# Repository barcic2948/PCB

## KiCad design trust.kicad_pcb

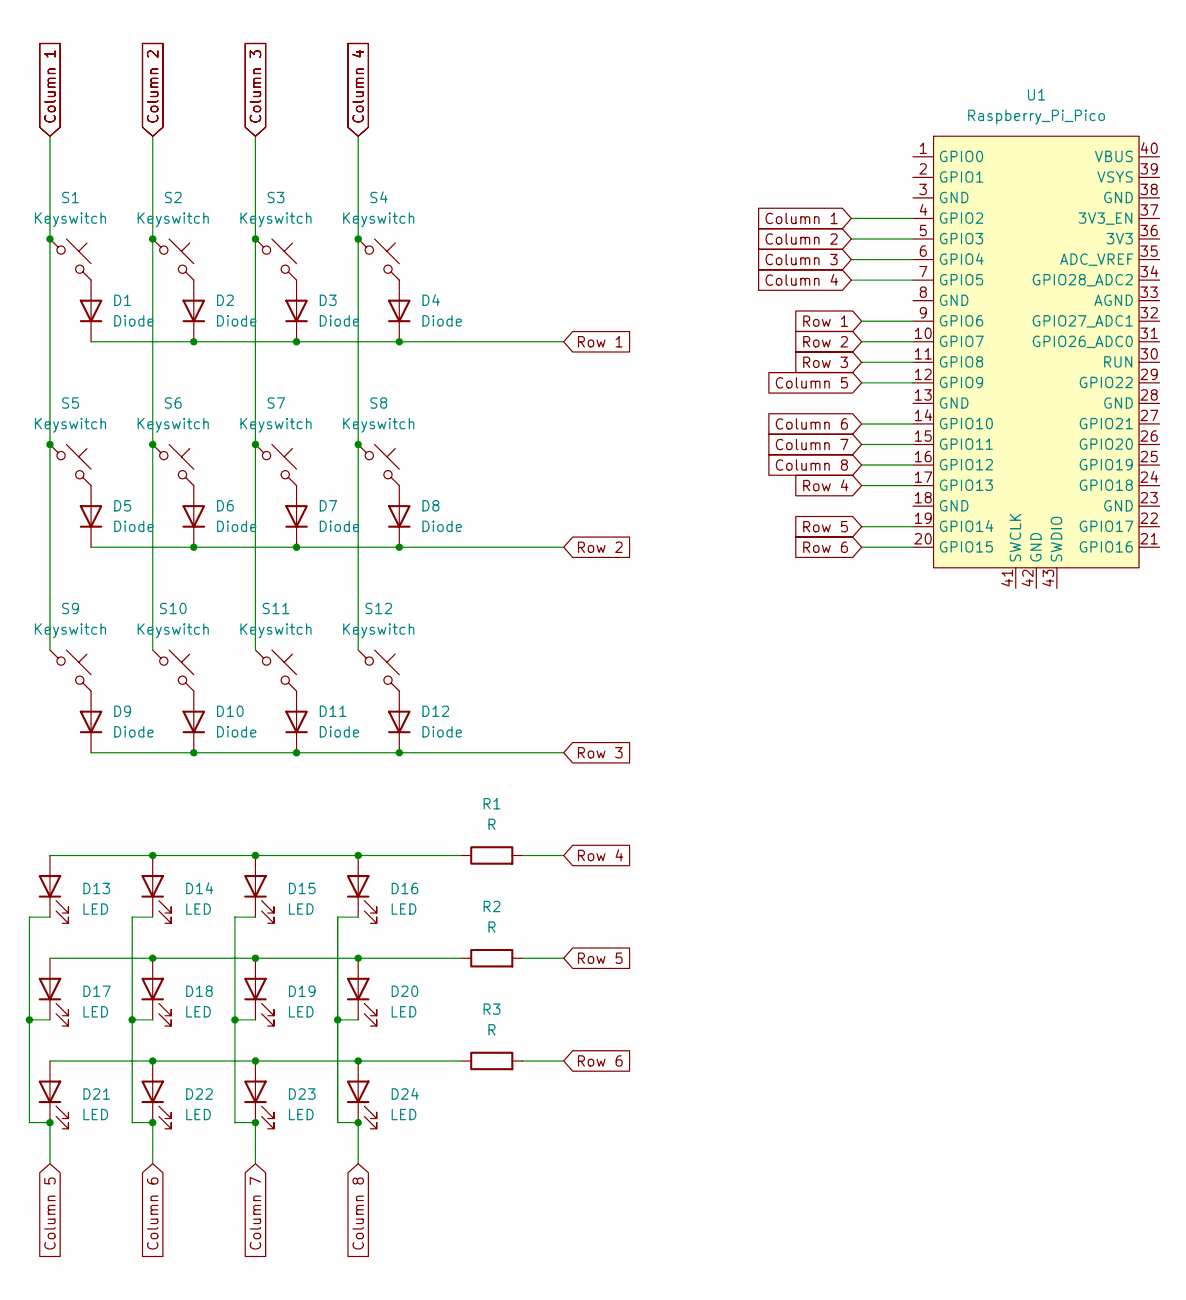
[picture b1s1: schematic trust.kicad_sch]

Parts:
D1, D2, D3, D4, D5, D6, D7, D8, D9, D10, D11, D12: Diode; Diode_DO-35
D13, D14, D15, D16, D17, D18, D19, D20, D21, D22, D23, D24: LED; LED_D1.8mm_W3.3mm_H2.4mm
R1, R2, R3: R; R_Axial_DIN0204_L3.6mm_D1.6mm_P5.08mm_Horizontal
S1, S2, S3, S4, S5, S6, S7, S8, S9, S10, S11, S12: Keyswitch; MX_PCB_1.00u
U1: Raspberry_Pi_Pico

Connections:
Column 1: S1.1, S5.1, S9.1, U1.4 (GPIO2)
Column 2: S2.1, S6.1, S10.1, U1.5 (GPIO3)
Column 3: S3.1, S7.1, S11.1, U1.6 (GPIO4)
Column 4: S4.1, S8.1, S12.1, U1.7 (GPIO5)
Column 5: D13.1 (K), D17.1 (K), D21.1 (K), U1.12 (GPIO9)
Column 6: D14.1 (K), D18.1 (K), D22.1 (K), U1.14 (GPIO10)
Column 7: D15.1 (K), D19.1 (K), D23.1 (K), U1.15 (GPIO11)
Column 8: D16.1 (K), D20.1 (K), D24.1 (K), U1.16 (GPIO12)
unnamed: D1.2 (A), S1.2
unnamed: D2.2 (A), S2.2
unnamed: D3.2 (A), S3.2
unnamed: D4.2 (A), S4.2
unnamed: D5.2 (A), S5.2
unnamed: D6.2 (A), S6.2
unnamed: D7.2 (A), S7.2
unnamed: D8.2 (A), S8.2
unnamed: D9.2 (A), S9.2
unnamed: D10.2 (A), S10.2
unnamed: D11.2 (A), S11.2
unnamed: D12.2 (A), S12.2
unnamed: D13.2 (A), D14.2 (A), D15.2 (A), D16.2 (A), R1.1
unnamed: D17.2 (A), D18.2 (A), D19.2 (A), D20.2 (A), R2.1
unnamed: D21.2 (A), D22.2 (A), D23.2 (A), D24.2 (A), R3.1
Row 1: D1.1 (K), D2.1 (K), D3.1 (K), D4.1 (K), U1.9 (GPIO6)
Row 2: D5.1 (K), D6.1 (K), D7.1 (K), D8.1 (K), U1.10 (GPIO7)
Row 3: D9.1 (K), D10.1 (K), D11.1 (K), D12.1 (K), U1.11 (GPIO8)
Row 4: R1.2, U1.17 (GPIO13)
Row 5: R2.2, U1.19 (GPIO14)
Row 6: R3.2, U1.20 (GPIO15)

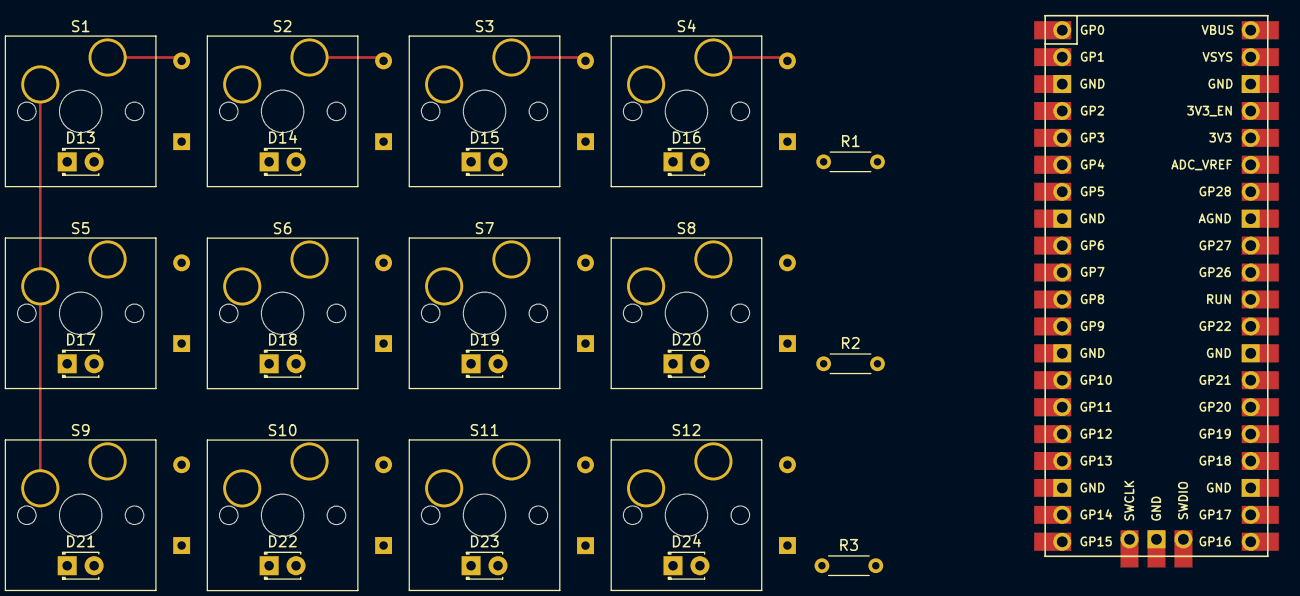
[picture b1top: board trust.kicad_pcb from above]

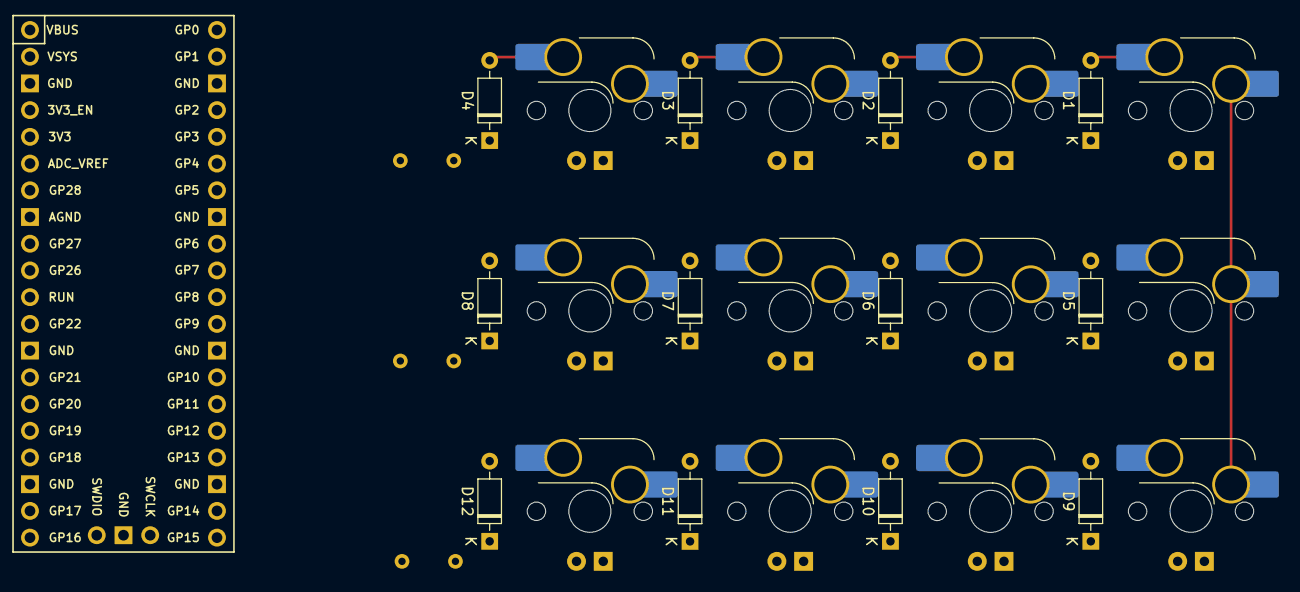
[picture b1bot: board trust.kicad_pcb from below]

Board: 2 copper layers, 40 parts (12 on the bottom side), 29 nets.
